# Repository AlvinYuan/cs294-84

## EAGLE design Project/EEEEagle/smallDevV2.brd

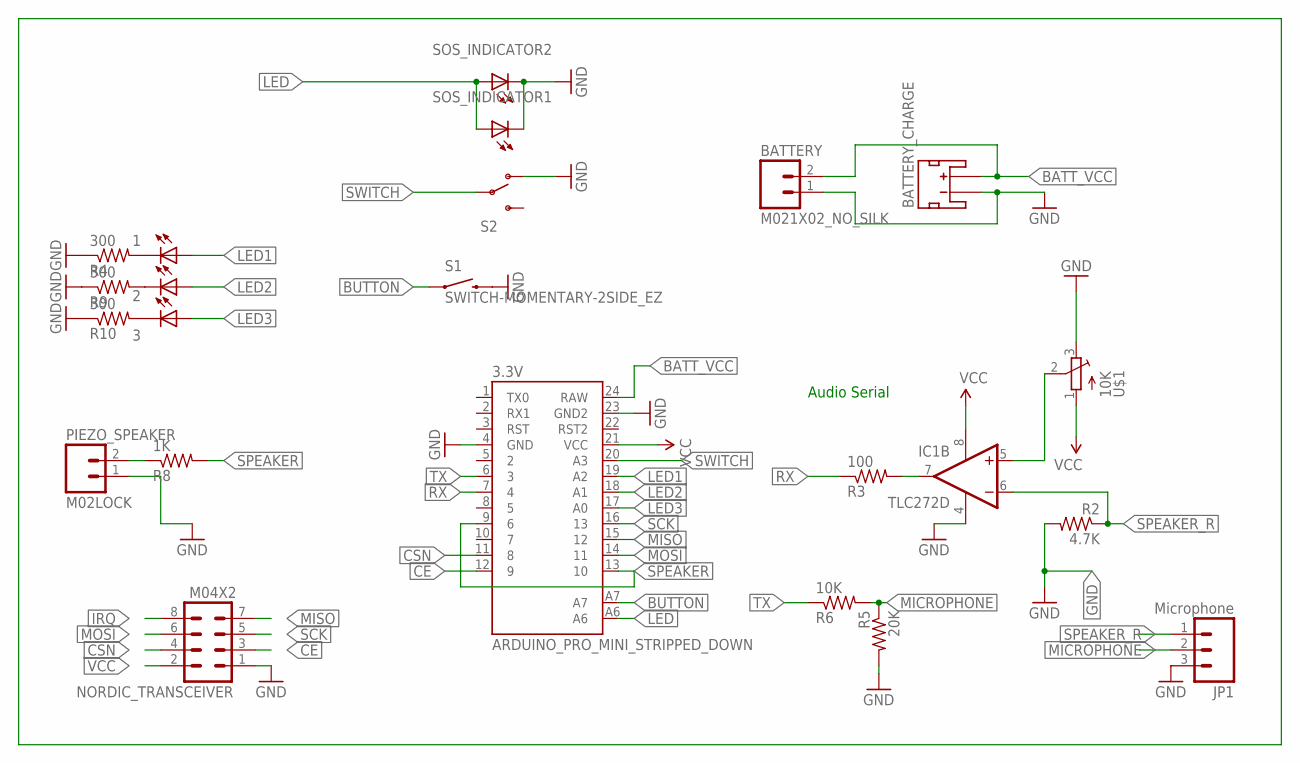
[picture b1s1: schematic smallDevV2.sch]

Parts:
1, 2, 3: LEDCHIP-LED0805; CHIP-LED0805
3.3V: ARDUINO_PRO_MINI_STRIPPED_DOWN
BATTERY: M021X02_NO_SILK; 1X02_NO_SILK
BATTERY_CHARGE: JST_2MM_MALE; JST-2-SMD
IC1: TLC272D; SO08
JP1: Microphone; 1X03_LOCK
NORDIC_TRANSCEIVER: M04X2; 2X4
PIEZO_SPEAKER: M02LOCK; 1X02_LOCK
R2: 4.7K; M0805
R3: 100; M0805
R4, R9, R10: 300; M0805
R5: 20K; M0805
R6: 10K; M0805
R8: 1K; M0805
S1: SWITCH-MOMENTARY-2SIDE_EZ; TACTILE-PTH-SIDEEZ
S2: SWITCH-SPDT-SMD-A; SWITCH-SPST-SMD-A
SOS_INDICATOR1, SOS_INDICATOR2: LEDCHIP-LED0805; CHIP-LED0805
U$1: 10K; TC33X

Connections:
BATT_VCC: 3.3V.24 (RAW), BATTERY.2, BATTERY_CHARGE.2 (+)
BUTTON: 3.3V.A7, S1.1
CE: 3.3V.12 (9), NORDIC_TRANSCEIVER.3
CSN: 3.3V.11 (8), NORDIC_TRANSCEIVER.4
GND: 3.3V.4 (GND), 3.3V.23 (GND2), BATTERY.1, BATTERY_CHARGE.1 (-), IC1.4 (V-), JP1.3, NORDIC_TRANSCEIVER.1, PIEZO_SPEAKER.1, R2.2, R4.1, R5.2, R9.1, R10.1, S1.2, S2.1 (O), SOS_INDICATOR1.C, SOS_INDICATOR2.C, U$1.3 (E)
IRQ: NORDIC_TRANSCEIVER.8
LED: 3.3V.A6, SOS_INDICATOR1.A, SOS_INDICATOR2.A
LED1: 1.A, 3.3V.19 (A2)
LED2: 2.A, 3.3V.18 (A1)
LED3: 3.A, 3.3V.17 (A0)
MICROPHONE: JP1.2, R5.1, R6.2
MISO: 3.3V.15 (12), NORDIC_TRANSCEIVER.7
MOSI: 3.3V.14 (11), NORDIC_TRANSCEIVER.6
unnamed: IC1.5 (+IN), U$1.2 (S)
unnamed: IC1.7 (OUT), R3.2
unnamed: 1.C, R4.2
unnamed: PIEZO_SPEAKER.2, R8.1
unnamed: 2.C, R9.2
unnamed: 3.C, R10.2
RX: 3.3V.7 (4), R3.1
SCK: 3.3V.16 (13), NORDIC_TRANSCEIVER.5
SPEAKER: 3.3V.9 (6), 3.3V.13 (10), R8.2
SPEAKER_R: IC1.6 (-IN), JP1.1, R2.1
SWITCH: 3.3V.20 (A3), S2.2
TX: 3.3V.6 (3), R6.1
VCC: 3.3V.21 (VCC), IC1.8 (V+), NORDIC_TRANSCEIVER.2, U$1.1 (A)

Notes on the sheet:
Audio Serial

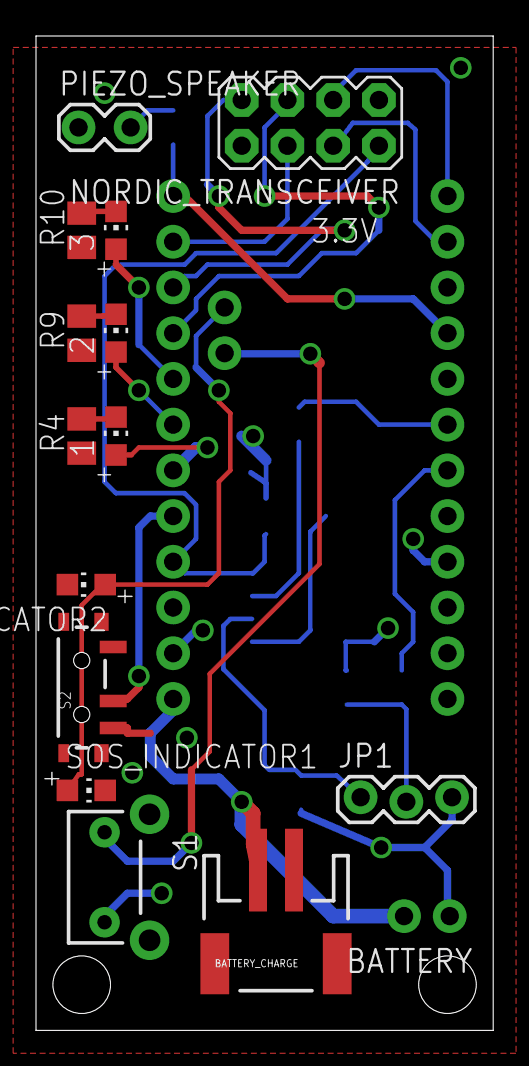
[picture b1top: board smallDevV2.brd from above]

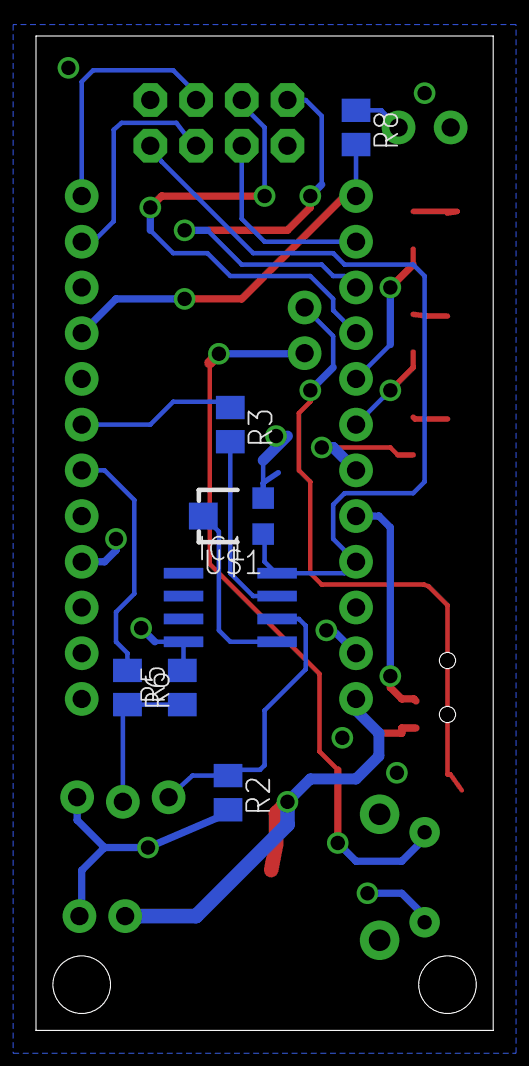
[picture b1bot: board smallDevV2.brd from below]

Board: 2 copper layers, 25.4 x 55.2 mm, 23 parts (7 on the bottom side), 25 nets.

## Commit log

2013-09-19 Initial commit. HW2
2013-09-26 test code with capacitive sensor and fsr
2013-09-29 comments updated and fritz added
2013-10-30 Project XBee prototype arduino code
2013-11-04 project prototype code
2013-11-04 Prototype android app
2013-11-08 audioserial from phone to arduino
2013-11-08 first commit of mesh code
2013-11-08 updated pingpair_modified
2013-11-08 updated code for pingpair, servo works
2013-11-08 blahehehhaefa
2013-11-08 pingpair_original
2013-11-08 rename
2013-11-08 a;wioefj;aioweg
2013-11-08 changes with phone talking to arduino to nordic
2013-11-08 update clearer roles for ping and pong
2013-11-08 AudioSerial receive
2013-11-08 new commits
2013-11-17 Nordic common sketch.
2013-11-18 some improvements to audio serial.
2013-11-23 audio serial improved. 300 baudrate supported
2013-11-23 Audio Serial strings and software serial
2013-11-24 cleaned up code organization
2013-11-24 created send alerts page and alerts log page
2013-11-24 created alerts map page
2013-11-25 CAD for device container
2013-11-25 cleanup android project to compile
2013-11-25 Push eagle files v1
2013-11-25 updated CAD
2013-12-03 basic microphone communication working
2013-12-03 microphone baudrate to 100 and cleanup
2013-12-04 commit yo
2013-12-04 device controller arduino code. not tested. compiles
2013-12-06 updates to device controller arduino code. tested basic phone to radio communication
2013-12-06 device controller tested for the most part.
2013-12-06 mobile app UI/backend functionality
2013-12-06 fixes to mobile app
2013-12-06 mobile app checked Radio ID added to string msg
2013-12-06 pin changes for schematic
2013-12-06 pin numbers update again (breadboard pins updated).
2013-12-07 audioserial rx on android side now is async task. packet class. clean up on audioserial
2013-12-07 some small additions and cleanup
2013-12-07 basic packet protocol
2013-12-07 more packet parsing. Alerts log view
2013-12-07 update pins pre nordic library changes
2013-12-08 audio serial improved and works with pro mini.
2013-12-08 updated schematic and board. nordic pins fixed to use SPI bus.
2013-12-08 pins updated and cleanup.
2013-12-08 LED code (tested). nordic_common can send custom messages via serial terminal. Packet protocol added to arduino. Code cleanup and rearranged.
2013-12-08 google maps loading. Need to follow google docs for setting this up (involves reading SHA1 key and obtaining android api key
2013-12-09 compatible and working with lower version phone (Kevin's)
2013-12-09 current location and basic maps.
2013-12-09 newest pins with PCB.
2013-12-09 Ui prettify
2013-12-09 color map
2013-12-09 do not invert software serial to match device circuit
2013-12-09 Lanssie's UI improvements + some more from Alvin
2013-12-09 fix map marker onCliick
2013-12-09 Fake tabs. Lots of reorganizing.
2013-12-09 improve list view appearance
2013-12-09 log view header matches others
2013-12-09 better packet generated data and better map view UI
2013-12-09 icon updates
2013-12-09 font style changes and danger view improved
2013-12-09 action bar name fixed and manifest cleanup
2013-12-09 icon update
2013-12-09 moved danger send message button. added screenshots
2013-12-10 phone now parses and sends latlng data
2013-12-10 SOS phone working
2013-12-11 piezo, danger button flash, and reversed switch logic so ON is up on the device
2013-12-11 SOS screen
2013-12-11 phone improvements and cleanup. base station controller
2013-12-12 ring buffering of packets
2013-12-12 radio button group fixed
2013-12-12 debug code on phone. 32 byte max packet size to match radio. small bug fixes

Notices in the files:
parts and their libraries:
SparkFun-Connectors: Licensing: CC v3.0 Share-Alike You are welcome to use this library for commercial purposes.
